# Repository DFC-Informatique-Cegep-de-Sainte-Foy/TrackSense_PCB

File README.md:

# TrackSense PCB

## Un protoype expérimental pour le projet [TrackSense](https://github.com/DFC-Informatique-Cegep-de-Sainte-Foy/TrackSense)

**:warning: <span style="color:red">Avertissement: ce design n'a pa été ni contruit ni testé. Ce dépôt n'offre aucune garantie quant au fonctionnement du prototype. Procédez à la fabrication à vos risques.</span>**

Créé avec le logiciel open source gratuit [KiCad V8.0.0](https://gitlab.com/kicad)

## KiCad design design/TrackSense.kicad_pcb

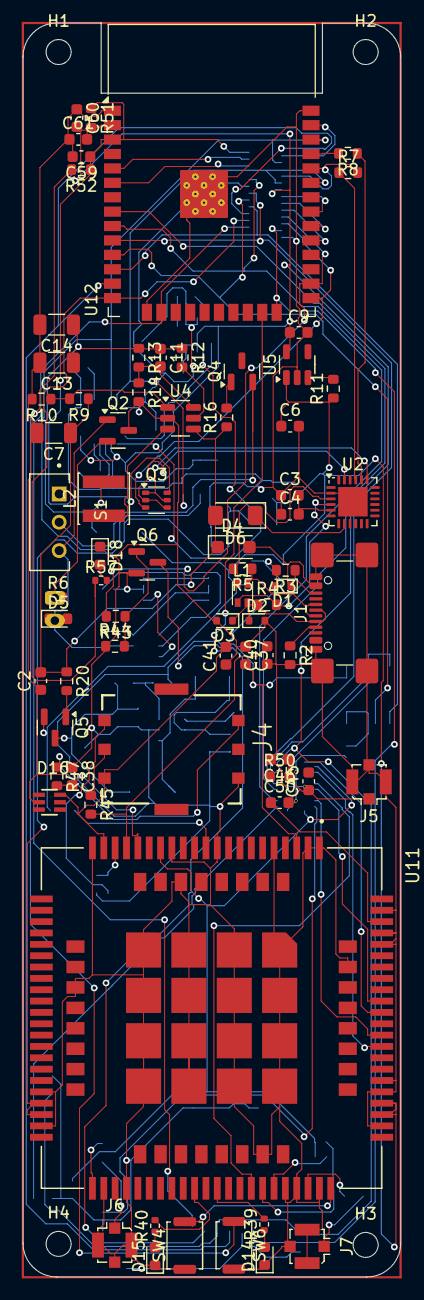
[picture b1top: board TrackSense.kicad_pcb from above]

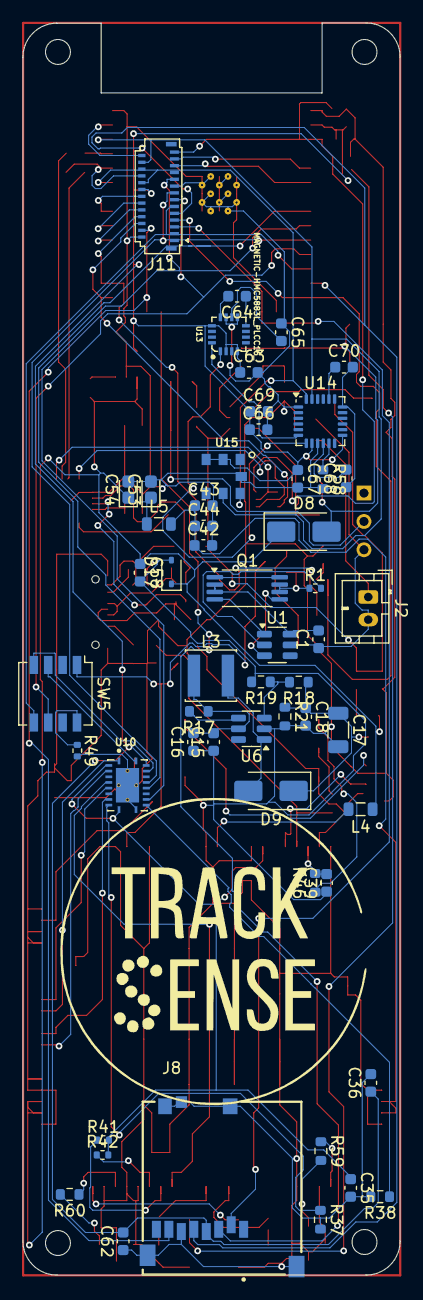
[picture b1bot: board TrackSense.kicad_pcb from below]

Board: 2 copper layers, 33.3 x 110.5 mm, 132 parts (54 on the bottom side), 107 nets.

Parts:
C1: 1nF; C_0603_1608Metric
C2, C4, C43, C44: 10uF; C_0603_1608Metric
C3: 100uF; C_0603_1608Metric
C6, C9, C35, C36, C46, C62: 100nF; C_0603_1608Metric
C7, C13, C14, C17: 22uF_10V; C_1206_3216Metric
C11: 47pF; C_0603_1608Metric
C15, C61: 10u; C_0603_1608Metric
C16: 1uf; C_0603_1608Metric
C18, C37, C41, C58: 0.1uF; C_0603_1608Metric
C38, C39, C40: 22uF; C_0603_1608Metric
C42, C59: 1uF; C_0603_1608Metric
C45, C50: 33pF; C_0603_1608Metric
C53, C54: 100uF; CP_EIA-1608-08_AVX-J
C60, C63, C66, C67, C68, C69: 0u1f; C_0603_1608Metric
C64: 220uf; C_0603_1608Metric
C65: 4.7uf; C_0603_1608Metric
C70: 2200pf; C_0603_1608Metric
D1, D2, D3: LESD5D5.0CT1G; D_SOD-523
D4: STPST1H100ZFY; D_SOD-123F
D5: YELLOW; LED_0603_1608Metric
D6: LL4148; D_MiniMELF
D8, D9: SS34; D_SMA
D14, D15: RED; LED_0603_1608Metric
D16: SMF05C; SOT65P210X110-6N
D17: PESDHC3D3V3U; D_SOD-323
D18: BLUE; LED_0603_1608Metric
H1, H2, H3, H4: MountingHole; MountingHole_2.2mm_M2_ISO7380
J1: C2765186; USB_C_Receptacle_GCT_USB4110
J2: Conn_01x02_Socket; JST_PH_B2B-PH-K_1x02_P2.00mm_Vertical
J4: SIM_Card; GCT_SIM8051-6-0-14-00-X-REVD
J5: GNSS_Coaxial_Small; U.FL_Molex_MCRF_73412-0110_Vertical
J6: MAIN_Coaxial_Small; U.FL_Molex_MCRF_73412-0110_Vertical
J7: AUX_Coaxial_Small; U.FL_Molex_MCRF_73412-0110_Vertical
J8: MEM2052-00-195-00-A_REVA; GCT_MEM2052-00-195-00-A_REVA
J11: Conn_01x28; Hirose_FH26-27S-0.3SHW_2Rows-27Pins-1MP_P0.60mm_Horizontal
L1: L_Ferrite_Coupled_1423; L_CommonModeChoke_Coilcraft_0805USB
L2: 1.5uH-DCR<0.1R-3A; L_Sunlord_SWPA4010S
L3: 4.7uH/3A; L_Sunlord_SWPA4010S
L4, L5: 100MHz 220ohm; L_0805_2012Metric
Q1: FS8205A; TSSOP-8_4.4x3mm_P0.65mm
Q2: AO3400A; SOT-23
Q3: UMH3N; SOT-363_SC-70-6
Q4, Q5: AO3401A; SOT-23
Q6: MMBT3904; SOT-23
R1: 1k; R_0402_1005Metric
R2, R3: 5.1k; R_0603_1608Metric
R4, R5: 10; R_0603_1608Metric
R6: 10k; R_0402_1005Metric
R7, R8: 470; R_0603_1608Metric
R9, R10, R21: 100K; R_0603_1608Metric
R11, R12, R17: 10K; R_0603_1608Metric
R13, R18: 120K_1%; R_0603_1608Metric
R14, R19: 20K_1%; R_0603_1608Metric
R16, R20: 100R; R_0603_1608Metric
R37, R38: 47k; R_0603_1608Metric
R39, R40: 390R; R_0402_1005Metric
R41, R42, R49: 10K; R_0402_1005Metric
R43: 4.7K; R_0603_1608Metric
R44: 47K; R_0603_1608Metric
R45, R46, R47, R52: 22R; R_0603_1608Metric
R50, R59, R60: 0R; R_0603_1608Metric
R51: 10k; R_0603_1608Metric
R57: 1K; R_0402_1005Metric
R58: 1k; R_0603_1608Metric
S1: EG1270; SW_EG1270
SW4: BOOT_CFG; SW_Push_SPST_NO_Alps_SKRK
SW5: SW_DIP_x04; SW_DIP_SPSTx04_Slide_Copal_CHS-04A_W5.08mm_P1.27mm_JPin
SW6: RESET; SW_Push_SPST_NO_Alps_SKRK
U1: WSTDW01; SOT-23-6
U2: CP2104; QFN-24-1EP_4x4mm_P0.5mm_EP2.6x2.6mm
U4: JW5222; SOT-23-6
U5: ME6217; SOT-23-5
U6: TCS9208; SOT-23-6
U10: TXB0108RGYR; IC_TXB0108RGYR
U11: SIM7600G; IC_SIM7600G
U12: ESP32-WROVER-B; ESP32-WROOM-32
U13: MAGNETIC-HMC5883L_PLCC16_; PLCC16-0.5-3X3MM
U14: MPU-6050; InvenSense_QFN-24_4x4mm_P0.5mm
U15: PRESSURE-BMP180_LGA7_; LGA7-1.5-3.8X3.6MM

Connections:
AUX_ANT: R60.1, U11.59 (AUX_ANT)
D+: J1.A6 (D+), J1.B6 (D+), L1.2, R5.1
D-: D2.1 (A1), D3.1 (A1), J1.A7 (D-), J1.B7 (D-), L1.1, R4.1
DM: L1.4, R4.2, U2.4 (D-)
DP: L1.3, R5.2, U2.3 (D+)
DTR: Q3.2 (B1), Q3.4 (E2), U2.23 (~DTR)
DVDD4V2: C6.1, C53.1, C54.1, C58.1, D8.1 (K), D17.1 (K), L4.1, L5.1, Q5.2 (S), R11.1, U5.1 (VIN), U11.62 (VBAT), U11.63 (VBAT)
FLIGHTMODE: U10.5 (A4), U11.54 (FLIGHTMODE)
G2: Q1.5, U1.3 (CO)
GND: C2.1, C3.1, C4.1, C6.2, C7.2, C9.2, C13.2, C14.2, C15.1, C16.1, C17.2, C18.2, C35.2, C36.2, C37.1, C38.1, C39.1, C40.1, C41.1, C42.2, C43.2, C44.2, C45.2, C46.2, C53.2, C54.2, C58.2, C59.2, C60.1, C61.1, C62.1, C63.2, C65.1, C66.2, C67.2, C68.1, C69.2, C70.2, D1.2 (A2), D2.2 (A2), D3.2 (A2), D14.1 (K), D15.1 (K), D16.2, D17.2 (A), D18.1 (K), J1.A1 (GND), J1.A12 (GND), J1.B1 (GND), J1.B12 (GND), J1.S1 (SHIELD), J4.5 (GND), J5.2 (Ext), J6.2 (Ext), J7.2 (Ext), J8.G1 (SHIELD_GND), J8.G2 (SHIELD_GND), J8.G3 (SHIELD_GND), J8.G4 (SHIELD_GND), J8.P6 (VSS), J8.P9 (CD_PIN), J11.2, J11.17, Q1.6, Q1.7, Q2.3 (D), Q6.2 (E), R1.1, R2.2, R3.2, R10.2, R14.2, R19.2, R21.2, R37.2, R38.2, R44.1, R49.2, R58.2, SW4.1, SW6.2, U2.2 (GND), U2.25 (GND), U4.2 (GND), U5.2 (VSS), U6.2 (GND), U10.11 (GND), U10.21 (EXP), U10.21_1 (EXP), U10.21_2 (EXP), U10.21_3 (EXP), U10.21_4 (EXP), U11.1 (GND), U11.2 (GND), U11.5 (GND), U11.10 (GND), U11.14 (GND), U11.37 (GND), U11.40 (GND), U11.41 (GND), U11.43 (GND), U11.57 (GND), U11.58 (GND), U11.60 (GND), U11.61 (GND), U11.64 (GND), U11.65 (GND), U11.77 (GND), U11.78 (GND), U11.80 (GND), U11.81 (GND), U11.93 (GND), U11.98 (GND), U11.110 (GND), U11.118 (GND), U11.120 (GND), U11.121 (GND), U11.122 (GND), U11.123 (GND), U11.124 (GND), U11.125 (GND), U11.126 (GND), U11.127 (GND), U11.128 (GND), U11.129 (GND), U11.130 (GND), U11.131 (GND), U11.132 (GND), U11.133 (GND), U11.134 (GND), U11.135 (GND), U12.1 (GND), U12.15 (GND), U12.38 (GND), U12.39 (GND), U13.9 (9(GND)), U13.11 (11(GND)), U14.1 (CLKIN), U14.9 (AD0), U14.18 (GND), U15.7 (GND)
GNSS_ANT: C50.1, U11.79 (GNSS_ANT)
GPIO26: SW5.3, U10.20 (B1)
GPIO27: SW5.4, U10.18 (B2)
IO0: J11.6, Q3.3 (C2), U12.25 (IO0)
IO2: J8.P7 (DAT0), J11.4, U12.24 (IO2)
IO4: J11.8, R43.2, U12.26 (IO4)
IO5: J11.10, U12.29 (IO5)
IO12: J11.7, R57.1, U12.14 (IO12)
IO13: J8.P2 (CD/DAT3), J11.5, U12.16 (IO13)
IO14: J8.P5 (CLK), J11.9, U12.13 (IO14)
IO15: J8.P3 (CMD), J11.3, U12.23 (IO15)
IO18: J11.12, U12.30 (IO18)
IO19: J11.14, U12.31 (IO19)
IO21: J11.18, U12.33 (IO21), U14.24 (SDA), U15.6 (SDA)
IO22: J11.24, U12.36 (IO22), U14.23 (SCL), U15.5 (SCL)
IO23: J11.26, U12.37 (IO23)
IO25: J11.15, U10.16 (B4), U12.10 (IO25)
IO26: J11.13, SW5.6, U12.11 (IO26)
IO27: J11.11, SW5.5, U12.12 (IO27)
IO32: J11.21, U10.15 (B5), U12.8 (IO32)
IO33: J11.19, U10.13 (B7), U12.9 (IO33)
IO34: J11.23, U12.6 (IO34)
MAIN_ANT: R59.1, U11.82 (MAIN_ANT)
unnamed: D1.1 (A1), D4.2 (A), J1.A4 (VBUS), J1.A9 (VBUS), J1.B4 (VBUS), J1.B9 (VBUS)
unnamed: D5.2 (A), R6.2
unnamed: D6.1 (K), U2.8 (VBUS)
unnamed: D9.2 (A), L3.2, U6.1 (SW)
unnamed: D14.2 (A), R39.1
unnamed: D15.2 (A), R40.1
unnamed: D18.2 (A), R57.2
unnamed: J1.A5 (CC1), R2.1
unnamed: J1.B5 (CC2), R3.1
unnamed: J2.1, Q2.2 (S), R6.1
unnamed: J4.3 (CLK), R46.1
unnamed: J4.7 (I/O), R47.1
unnamed: J4.2 (RST), R45.1
unnamed: C45.1, C46.1, C50.2, J5.1 (In), R50.2
unnamed: J6.1 (In), R59.2
unnamed: J7.1 (In), R60.2
unnamed: Q1.1, Q1.8
unnamed: Q4.1 (G), R16.2
unnamed: Q5.1 (G), R20.2
unnamed: Q6.1 (B), R43.1, R44.2
unnamed: R49.1, SW5.8
unnamed: R52.2, SW6.1
unnamed: Q1.4, U1.1 (DO)
unnamed: R1.2, U1.2 (VM)
unnamed: R8.1, U2.20 (RXD)
unnamed: R7.1, U2.21 (TXD)
unnamed: R9.2, R10.1, U4.1 (EN)
unnamed: C11.2, R13.2, R14.1, U4.6 (FB)
unnamed: R12.2, U4.5 (PG)
unnamed: L2.1, U4.3 (SW)
unnamed: R11.2, U5.3 (CE)
unnamed: R17.2, U6.4 (EN)
unnamed: R18.2, R19.1, U6.3 (FB)
unnamed: R37.1, U10.9 (A8)
unnamed: R38.1, U10.12 (B8)
unnamed: SW4.2, U11.85 (BOOT_CFG0/USB_BOOT)
unnamed: R39.2, U11.51 (NETLIGHT)
unnamed: L4.2, U11.11 (USB_VBUS)
unnamed: C64.1, U13.8 (8(SETP))
unnamed: C65.2, U13.10 (10(C1))
unnamed: C64.2, U13.12 (12(SETC))
unnamed: C70.1, U14.20 (CPOUT)
unnamed: R58.1, U14.11 (FSYNC)
unnamed: C68.2, U14.10 (REGOUT)
PWRKEY: C37.2, Q6.3 (C), SW5.1, U11.3 (~PWRKEY)
RST/EN: C59.1, J11.27, Q3.6 (C1), R51.1, R52.1, U12.3 (EN)
RTS: Q3.1 (E1), Q3.5 (B2), U2.19 (~RTS)
SCL: R41.1, U11.55 (SCL)
SDA: R42.1, U11.56 (SDA)
SIM_CLK: C39.2, R46.2, U11.19 (USIM_CLK)
SIM_IO: C38.2, R47.2, U11.17 (USIM_DATA)
SIM_RST: C40.2, R45.2, U11.18 (USIM_RST)
STATUS: R40.2, U11.49 (STATUS)
S_VN/39: J11.25, U12.5 (SENSOR_VN)
U0RXD: J11.20, R7.2, U12.34 (RXD0/IO3)
U0TXD: J11.22, R8.2, U12.35 (TXD0/IO1)
UART_DTR: U10.6 (A5), U11.72 (DTR)
UART_RI: U10.8 (A7), U11.69 (RI)
UART_RXD: U10.3 (A2), U11.68 (RXD)
UART_TXD: U10.1 (A1), U11.71 (TXD)
VBAT: C15.2, C16.2, L3.1, R17.1, U6.5 (IN)
VBAT-: C1.2, Q1.2, Q1.3, U1.6 (VSS)
VBUS: C2.2, C7.1, D4.1 (K), D6.2 (A), R9.1, R16.1, R20.1, U4.4 (VIN)
VCC3V3: C9.1, C36.1, C60.2, C61.2, C62.2, C63.1, C66.1, C67.1, C69.1, J8.P4 (VDD), J11.1, J11.16, R51.2, U5.5 (VOUT), U10.19 (VCCB), U12.2 (VDD), U13.2 (2(VDD)), U13.4 (4(S1)), U13.13 (13(VDDIO)), U14.8 (VLOGIC), U14.13 (VDD), U15.2 (VDD), U15.3 (VDDIO)
VCC_4V2: C11.1, C13.1, C14.1, D8.2 (A), L2.2, R12.1, R13.1
VCC_BAT: C1.1, D5.1 (K), J2.2, Q2.1 (G), S1.3, U1.5 (VDD)
VCC_MAIN: C42.1, C43.1, C44.1, L5.2, U11.38 (VBAT), U11.39 (VBAT)
VCC_UART: C3.2, C4.2, U2.5 (VIO)
VDD_1V8: C35.1, R41.2, R42.2, U10.2 (VCCA), U10.10 (OE), U11.15 (VDD_1V8)
VDD_4V2: C17.1, C18.1, D9.1 (K), Q5.3 (D), R18.1, R21.1
VSIM: C41.2, D16.6, J4.1 (VCC), U11.20 (USIM_VDD)
V_BAT: Q4.2 (S), S1.2
XCL: U13.1 (1(SCL)), U14.7 (AUX_CL)
XDA: U13.16 (16(SDA)), U14.6 (AUX_DA)

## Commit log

2024-05-09 update gitignore
2024-05-09 ajout design
2024-05-09 un début
2024-05-09 correction typo
2024-05-09 ajout 3d render raytraced
2024-05-11 more obvious warning
2024-05-11 span
2024-05-11 span misplaced
